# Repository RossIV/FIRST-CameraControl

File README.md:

# FIRST Camera Control

This repository contains code used by the [Georgia FIRST Robotics Competition](http://gafirst.org/) for remote-controlling [PTZ Optics 12X-SDI](http://ptzoptics.com/12x-sdi/) cameras using [Logitech Extreme 3D Pro](http://gaming.logitech.com/en-us/product/extreme-3d-pro-joystick) joysticks. The original code has been modified for use with [Marshall CV620-IP](http://www.marshall-usa.com/cameras/CV620-IP/index.php) cameras.

 ## Setup
 
 #### Dependencies
 
 This application depends on these widely-available packages: 
 
 * [Cmake](https://cmake.org/)
 * [Boost](http://www.boost.org/)
 * [SDL 2.0](https://www.libsdl.org/)
 * [YAML-CPP](https://github.com/jbeder/yaml-cpp)
 
 In Linux, these can be installed with the following command:
 
 ```
 sudo apt-get install cmake libsdl2-dev libboost-all-dev libyaml-cpp-dev
 ```
 
 #### Installation
 
 Clone this repository and run these commands from the FIRST-CameraControl folder:
 
 ```
 mkdir cmake-build-debug
 cd cmake-build-debug
 cmake ..
 make
 ```
 
 This will generate the _FIRST_CameraControl_ binary executable in the _cmake-build-debug_ folder.
 
 ## Usage
 
 #### Setup
 
 Ensure that config.yaml (in the _cmake-build-debug_ folder) contains correct information for your cameras. Follow the example already there to generate entries for each of your cameras.
 
 #### Run
 
 From a terminal, run `./FIRST_CameraControl`. It will tell you how many camera entries it found in the config file and how many joysticks it detects are connected to the computer. Messages will be displayed as the application connects to each camera. Once all are connected, you should be able to control the cameras from your joysticks.
 
 #### Controls
 
 Basic pan-tilt functionality is mapped to the joystick's x and y axes. The speed of these motions is controlled by the paddle at the base of the joystick.
 
 The camera can be zoomed in and out using the direction hat on top of the joystick. Push forward to zoom in, pull back to zoom out.

 The camera can be focused near and far using the direction hat on top of the joystick. Push left to focus near, push right to focus far.
 
 If the camera begins moving unexpectedly, pull the trigger button to send a stop command to the camera.
 
 The camera has the capacity to store 9, user-defined, preset positions. These positions can be recalled using the labeled buttons (3,5-12) on the top and base of the joystick.
  
 The thumb button on the side of the joystick will reset the connection to the camera. This should happen nearly immediately.
 
 #### Troubleshooting
 
 There are a variety of network issues which can cause connection errors between this software and the cameras. In the event of one of these issues, this software will disable the individual camera to prevent the interruption of control for other cameras. If this happens, push the reset button or restart the software once the issue has been resolved. 

 #### Additional Reference

 [Marshall Protocol Spec](http://www.marshall-usa.com/pdf/CV620_RS232-Commands.pdf)

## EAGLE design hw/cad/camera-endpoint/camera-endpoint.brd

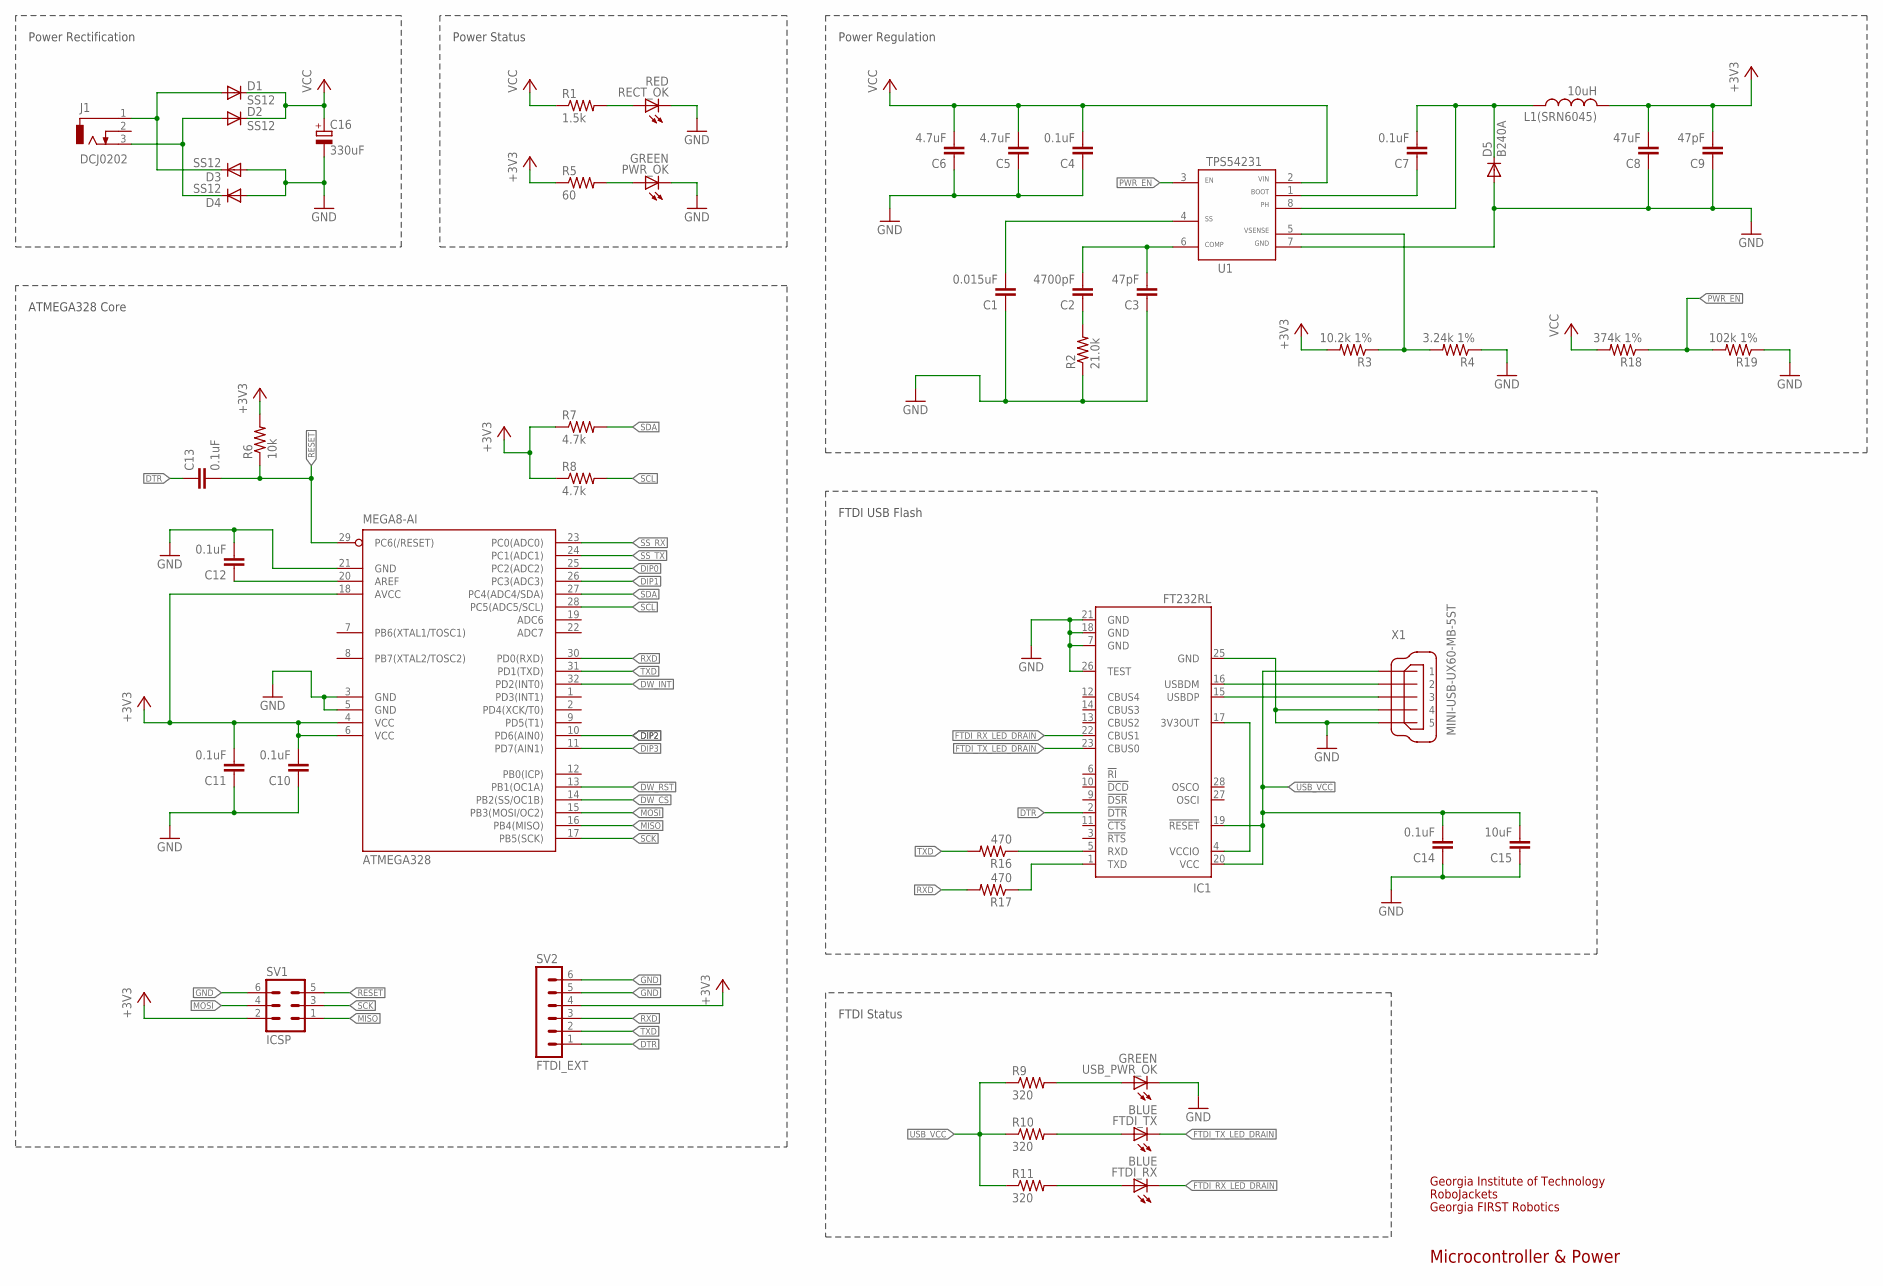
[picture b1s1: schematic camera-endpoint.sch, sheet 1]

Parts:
ATMEGA328: MEGA8-AI; TQFP32-08
C1: 0.015uF; C0603
C2: 4700pF; C0603
C3, C9: 47pF; C0603
C4, C7, C10, C11, C12, C13, C14: 0.1uF; C0603
C5, C6: 4.7uF; C0603
C8: 47uF; C1206
C15: 10uF; C0603
C16: 330uF; E5-8,5
D1, D2, D3, D4: SS12; DO214AC
D5: B240A; DO-214AC
FTDI_RX: BLUE; CHIP-LED0603
FTDI_TX: BLUE; CHIP-LED0603
IC1: FT232RL; SSOP28
J1: DCJ0202
L1(SRN6045): 10uH; POWER-CHOKE_WE-TPC
PWR_OK: GREEN; LED5MM
R1: 1.5k; R0603
R2: 21.0k; R0603
R3: 10.2k 1%; R0603
R4: 3.24k 1%; R0603
R5: 60; R0603
R6: 10k; R0603
R7, R8: 4.7k; R0603
R9, R10, R11: 320; R0603
R16, R17: 470; R0603
R18: 374k 1%; R0603
R19: 102k 1%; R0603
RECT_OK: RED; LED5MM
SV1: ICSP; MA03-2
SV2: FTDI_EXT; MA06-1
U1: TPS54231SO8; SO8
USB_PWR_OK: GREEN; CHIP-LED0603
X1: MINI-USB-UX60-MB-5ST; UX60-MB-5ST

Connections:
+3V3: ATMEGA328.4 (VCC), ATMEGA328.6 (VCC), ATMEGA328.18 (AVCC), C8.2, C9.2, C10.2, C11.2, L1(SRN6045).2, R3.2, R5.1, R6.2, R7.1, R8.1, SV1.2, SV2.4; also elsewhere on the board
DIP0: ATMEGA328.25 (PC2(ADC2)); also elsewhere on the board
DIP1: ATMEGA328.26 (PC3(ADC3)); also elsewhere on the board
DIP2: ATMEGA328.10 (PD6(AIN0)); also elsewhere on the board
DIP3: ATMEGA328.11 (PD7(AIN1)); also elsewhere on the board
DTR: C13.1, IC1.2 (!DTR), SV2.1
DW_CS: ATMEGA328.14 (PB2(SS/OC1B)); also elsewhere on the board
DW_INT: ATMEGA328.32 (PD2(INT0)); also elsewhere on the board
DW_RST: ATMEGA328.13 (PB1(OC1A)); also elsewhere on the board
FTDI_RX_LED_DRAIN: FTDI_RX.C, IC1.22 (CBUS1)
FTDI_TX_LED_DRAIN: FTDI_TX.C, IC1.23 (CBUS0)
GND: ATMEGA328.3 (GND), ATMEGA328.5 (GND), ATMEGA328.21 (GND), C1.1, C3.1, C4.1, C5.1, C6.1, C8.1, C9.1, C10.1, C11.1, C12.2, C14.1, C15.1, C16.-, D3.A, D4.A, D5.A, IC1.7 (GND), IC1.18 (GND), IC1.21 (GND), IC1.25 (GND), IC1.26 (TEST), PWR_OK.K (C), R2.1, R4.1, R19.1, RECT_OK.K (C), SV1.6, SV2.5, SV2.6, U1.7, USB_PWR_OK.C, X1.4, X1.5; also elsewhere on the board
MISO: ATMEGA328.16 (PB4(MISO)), SV1.1; also elsewhere on the board
MOSI: ATMEGA328.15 (PB3(MOSI/OC2)), SV1.4; also elsewhere on the board
unnamed: D1.A, D3.C, J1.1
unnamed: D2.A, D4.C, J1.3
unnamed: R1.2, RECT_OK.A
unnamed: C2.1, R2.2
unnamed: C7.1, U1.1
unnamed: C7.2, D5.C, L1(SRN6045).1, U1.8
unnamed: R3.1, R4.2, U1.5
unnamed: PWR_OK.A, R5.2
unnamed: ATMEGA328.20 (AREF), C12.1
unnamed: IC1.5 (RXD), R16.1
unnamed: IC1.4 (VCCIO), IC1.17 (3V3OUT)
unnamed: R9.2, USB_PWR_OK.A
unnamed: IC1.1 (TXD), R17.1
unnamed: IC1.16 (USBDM), X1.2
unnamed: IC1.15 (USBDP), X1.3
unnamed: FTDI_TX.A, R10.2
unnamed: FTDI_RX.A, R11.2
PWRREG_COMP: C2.2, C3.2, U1.6
PWRREG_SS: C1.2, U1.4
PWR_EN: R18.1, R19.2, U1.3
RESET: ATMEGA328.29 (PC6(/RESET)), C13.2, R6.1, SV1.5
RXD: ATMEGA328.30 (PD0(RXD)), R17.2, SV2.3
SCK: ATMEGA328.17 (PB5(SCK)), SV1.3; also elsewhere on the board
SCL: ATMEGA328.28 (PC5(ADC5/SCL)), R8.2; also elsewhere on the board
SDA: ATMEGA328.27 (PC4(ADC4/SDA)), R7.2; also elsewhere on the board
SS_RX: ATMEGA328.23 (PC0(ADC0)); also elsewhere on the board
SS_TX: ATMEGA328.24 (PC1(ADC1)); also elsewhere on the board
TXD: ATMEGA328.31 (PD1(TXD)), R16.2, SV2.2
USB_VCC: C14.2, C15.2, IC1.19 (!RESET), IC1.20 (VCC), R9.1, R10.1, R11.1, X1.1
VCC: C4.2, C5.2, C6.2, C16.+, D1.C, D2.C, R1.1, R18.2, U1.2; also elsewhere on the board

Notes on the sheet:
Power Rectification
Power Status
Power Regulation
ATMEGA328 Core
FTDI USB Flash
FTDI Status
Georgia Institute of Technology
RoboJackets
Georgia FIRST Robotics
Microcontroller & Power

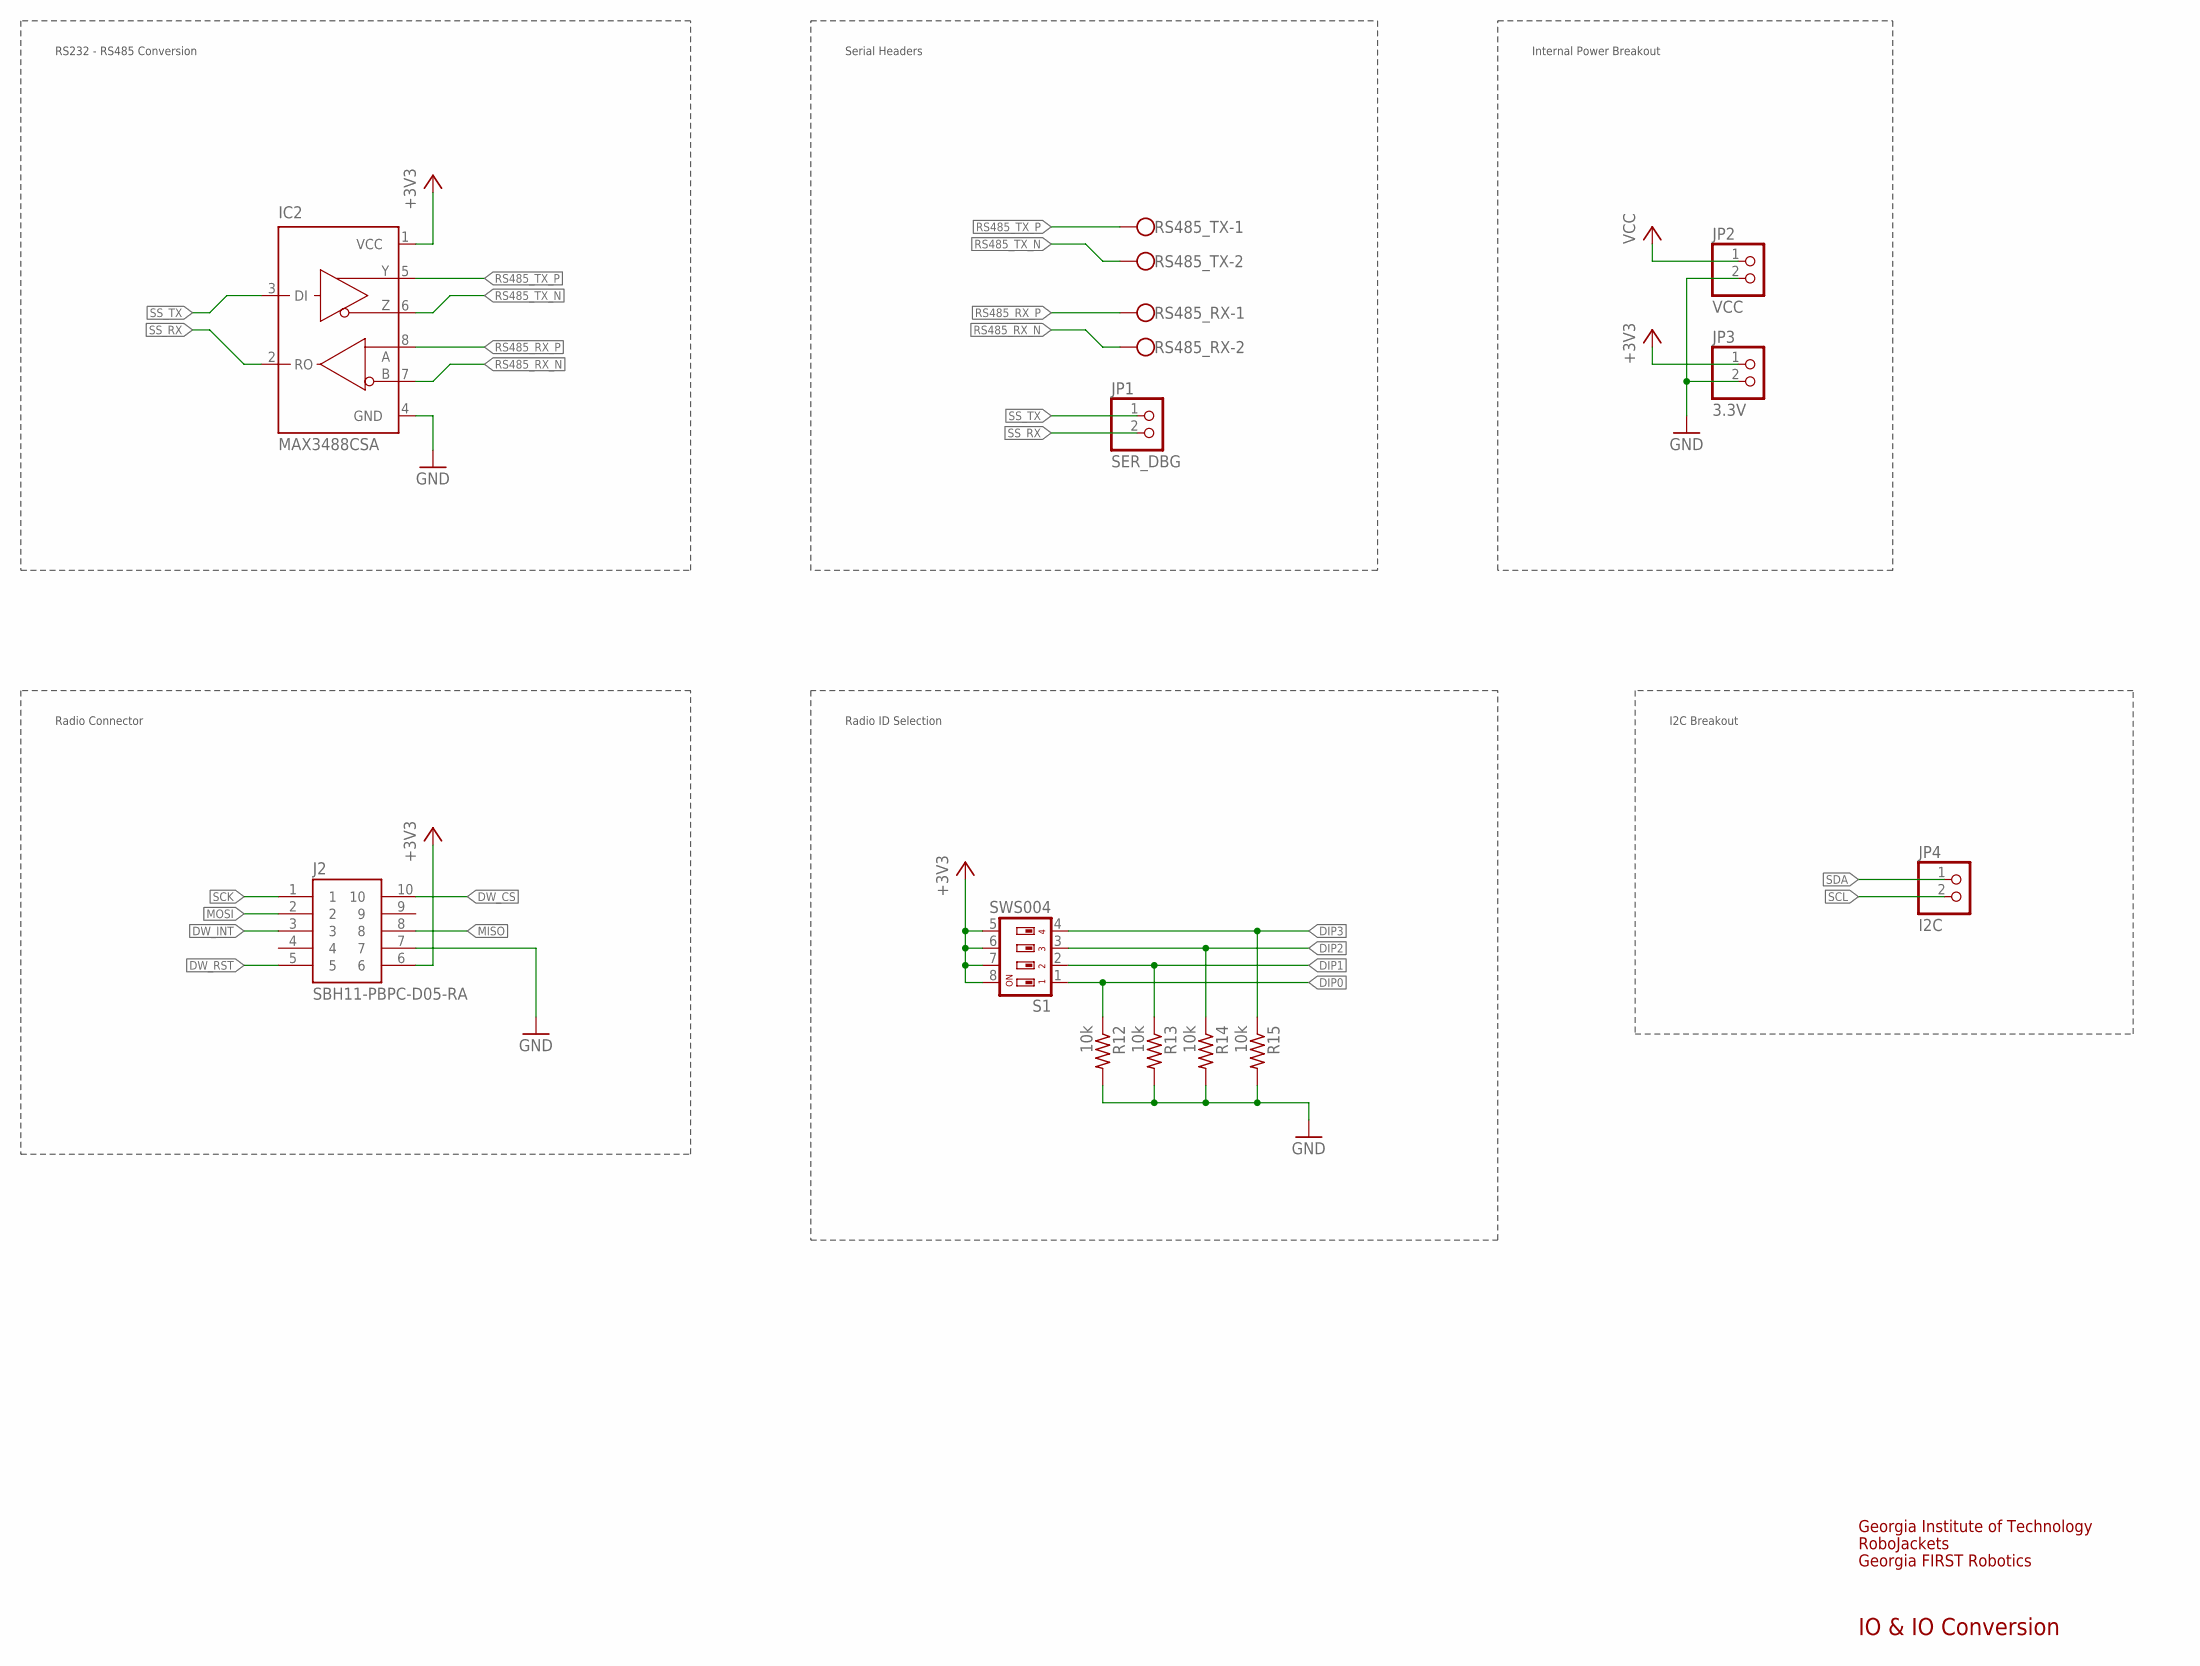
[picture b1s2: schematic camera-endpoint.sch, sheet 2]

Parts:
IC2: MAX3488CSA; SO08
J2: SBH11-PBPC-D05-RA; SBH11-*-D05-RA
JP1: SER_DBG; 1X02
JP2: VCC; 1X02
JP3: 3.3V; 1X02
JP4: I2C; 1X02
R12, R13, R14, R15: 10k; R0603
RS485_RX, RS485_TX: W237-102
S1: SWS004; SMS-004

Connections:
+3V3: IC2.1 (VCC), J2.6, JP3.1, S1.5, S1.6, S1.7, S1.8; also elsewhere on the board
DIP0: R12.1, S1.1; also elsewhere on the board
DIP1: R13.1, S1.2; also elsewhere on the board
DIP2: R14.1, S1.3; also elsewhere on the board
DIP3: R15.1, S1.4; also elsewhere on the board
DW_CS: J2.10; also elsewhere on the board
DW_INT: J2.3; also elsewhere on the board
DW_RST: J2.5; also elsewhere on the board
GND: IC2.4 (GND), J2.7, JP2.2, JP3.2, R12.2, R13.2, R14.2, R15.2; also elsewhere on the board
MISO: J2.8; also elsewhere on the board
MOSI: J2.2; also elsewhere on the board
RS485_RX_N: IC2.7 (B), RS485_RX.2
RS485_RX_P: IC2.8 (A), RS485_RX.1
RS485_TX_N: IC2.6 (Z), RS485_TX.2
RS485_TX_P: IC2.5 (Y), RS485_TX.1
SCK: J2.1; also elsewhere on the board
SCL: JP4.2; also elsewhere on the board
SDA: JP4.1; also elsewhere on the board
SS_RX: IC2.2 (RO), JP1.2; also elsewhere on the board
SS_TX: IC2.3 (DI), JP1.1; also elsewhere on the board
VCC: JP2.1; also elsewhere on the board

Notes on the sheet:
RS232 - RS485 Conversion
Radio ID Selection
Radio Connector
Serial Headers
Internal Power Breakout
I2C Breakout
Georgia Institute of Technology
RoboJackets
Georgia FIRST Robotics
IO & IO Conversion

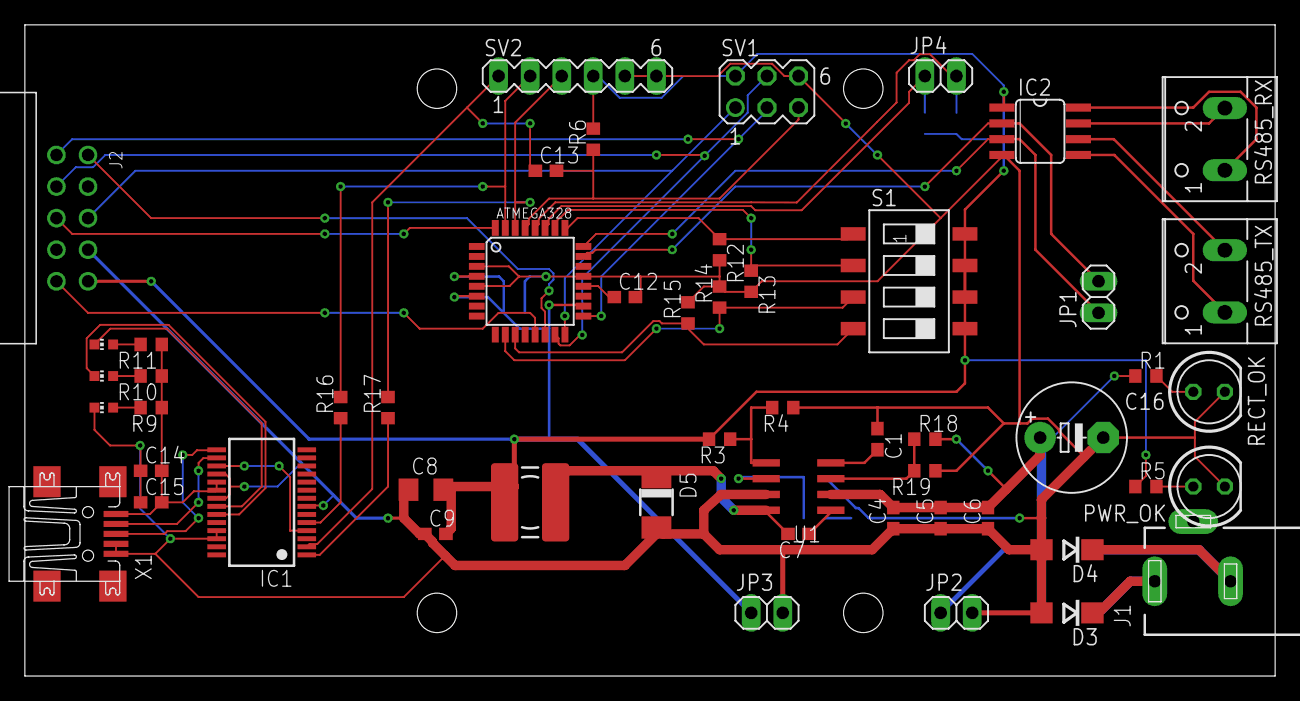
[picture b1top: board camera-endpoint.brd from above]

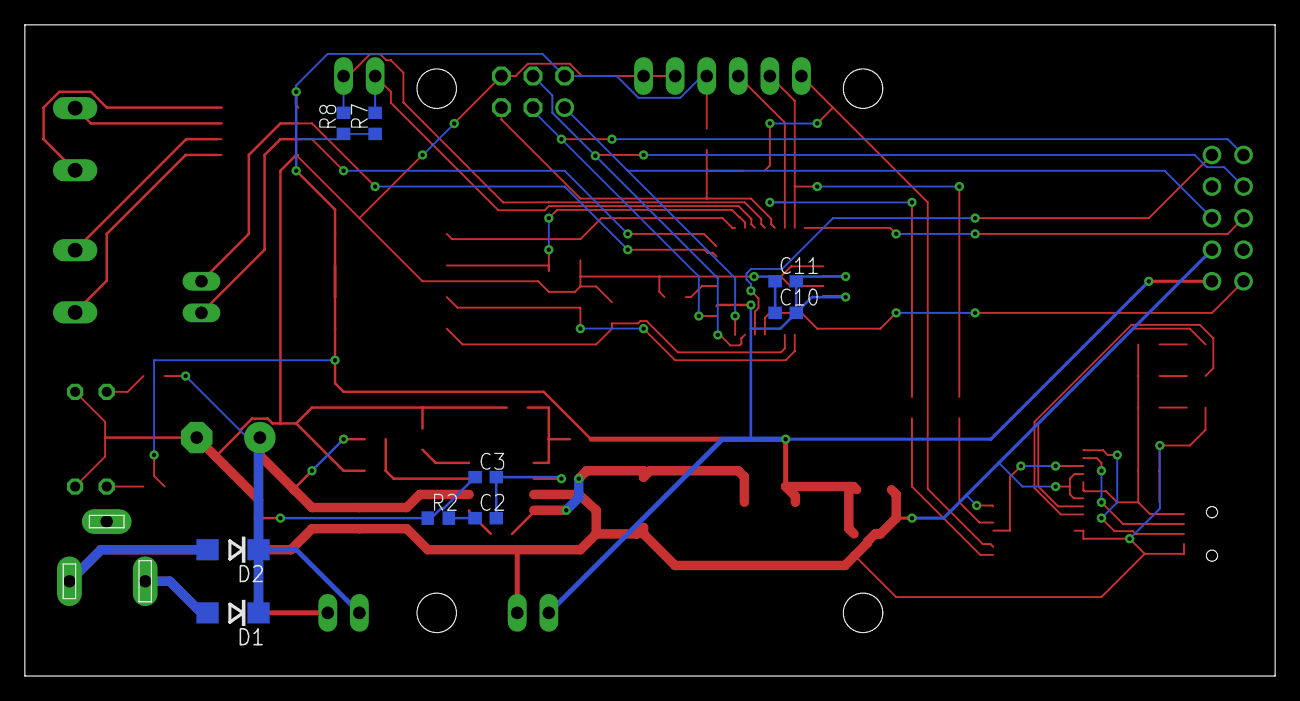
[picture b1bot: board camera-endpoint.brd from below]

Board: 2 copper layers, 100.6 x 52.4 mm, 62 parts (9 on the bottom side), 48 nets.

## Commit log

2017-09-15 stole and imported RoboCup radio board
2017-09-15 refactored production dirname to make BOMs fit in
2017-09-16 added voltage converter library from DIY modules
2017-09-17 added initial user-friendly BoM
2017-09-17 initial prototype of power, control, flash core
2017-09-17 cleaned MC/Power sheet, added authoring info
2017-09-17 generated web viewable image file
2017-09-17 refined symbology on sheet 1
2017-09-20 added Maxim lib for RS485 converter part
2017-09-20 finished serial conversion and IO in schematic
2017-09-20 updated schematic exports
2017-09-26 added dru
2017-09-28 fixed problems from design review
2017-09-28 routed board
2017-09-28 updates sch images
2017-09-28 added board images
2017-09-28 added Bill of Materials (BOM)
2017-09-28 organized dru files
2018-03-09 added auto indoor wb on reconnect
2018-03-13 fixed gitignore
2018-03-17 added dev setup script
2018-03-17 convert to tabs cuz I'm not a heathen
2018-03-21 Makes Camera constructor use CameraDetails struct.
2018-03-21 Replaces use of `std::shared_ptr` with movable Camera and Joystick objects.
2018-03-21 Moves deadzone setting into Controller constructor.
2018-03-21 General code cleanups / unused function removal.
2018-10-12 Change camera connection from tcp/5678 to udp/1259
2019-02-17 Initial tweaks to work with Marshall PTZ
2019-02-17 Fix preset save; Cleanup preset recall; Fix other camera rotate
2019-02-17 Update to reflect use with Marshall camera
2019-02-17 Generate message header in send_command() to clean up functions
2019-02-17 Rename 'command' to 'payload' for clarity
